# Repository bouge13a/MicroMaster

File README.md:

# The Next Generation of Hardware Hacking Tools
* The MicroMaster Mini, like the Bus-Pirate, Shikra, and Hydrabus before it, is a small circuit board that communicates to a computer via a Virtual COM port.
* The purpose of the MicroMaster Mini is to allow the user to test commands that may be sent from a master to a slave device using a variety of protocols such as UART, CAN, I2C, SMBUS, SPI, 1-Wire, WS2812 (neopixel) and PWM. The MicroMaster Mini also allows the user to "sniff" CAN, SMBUS, UART, and I2C transactions.
* Unlike the Bus-Pirate and Bus-Pirate derived devices, the MicroMaster Mini employs a highly sophisticated serial interface that has a system of pages similar to a web browser that can be navigated and manipulated with an ASCII keyboard. 
* Allows users to monitor the registers of I2C devices and SPI devices in real time. 
* Has an integrated help feature for each page which describes the purpose and operation of each page. The MicroMaster Mini does not require a manual for use. 
* Allows the user to easily manipulate 4 GPOs and monitor 4 GPIs and 4 ADCs. 
* Operates as an FTDI chip emulator so that the user can transmit UART signals to a USB virtual COM port. 
* Has a suite of neopixel control tools which allow the user to easily control up to 999 neopixels!
* Programmable power supply to 2v8 3v3 and 5v. The I2C bus also level shifts with the power supply. 
* The entire project is open sourced. 
* The MicroMaster Mini is based upon the TM4C123GXL launchpad and will run on a launchpad with some minor modifications. The code is written in C++ with FreeRTOS in the Code Composer Studio IDE.

Check out the demonstration video as well as other videos on the channel. Please like and subscribe for future videos. 

MicroMaster Mini Interface Demonstration (early version)
https://www.youtube.com/watch?v=Cxuv18Nnr2U&t=313s

Controlling Neopixels with the MicroMaster Mini
https://www.youtube.com/watch?v=bUdS3NqcU9w&t=137s

# Test and Build
The firmware will run on a TM4C123GXL launchpad. The following steps are the easiest way to test and build the MicroMaster Mini on a launchpad for testing. 

* Connect both USB ports to the host computer.
* Flash the .out file in the Debug directory to the TM4C123GXL using LMFlash (found on TI website)
* Set up a virtual COM port with the TM4C using Putty
* Start testing the MicroMaster Mini firmware! 
* Find a bug and report an issue.

Note: Some resistors will have to be removed from the launchpad to get full functionality (R9 and R10). The I2C sniffer will not work unless these resistors are removed.

# Get Involved!
The MicroMaster Mini is still very much under development. The purpose of making this project open sourced is to get the community involved. There is still a ton of work to do. If you have any of the following skills and would like to contribute, please email me at stephan@micromaster.io. I am very responsive, so don't hesitate to reach out. 

* C++ and FreeRTOS (expert)
* Bootloaders (OpenBLT)
* OpenOCD
* Web Design
* Testing and verification (open to all skill levels)
* Marketing
* Hardware Design
* Fundraising

# ScreenShots

Here is the first screen that comes up after the terminal detects a keystroke. The power supply is adjustable with the arrow keys and the user can press a corresponding letter to get to a tool suite. 

Here is the main suite of tools that are currently offered by the MicroMaster Mini. Press any letter to jump to a page or press TAB to toggle the pages. Press ESC to return to homepage. 

This is the configuration menu of the MicroMaster Mini. The user can select the configuration options by using the arrow keys

Here is an example of a transaction that was sent in I2C command. The transaction was set up so that it can be monitored on the next page. 

Here is the i2c monitor after a monitored transaction was sent. The value is periodically updated in real time. It can be converted to binary, hexidecimal, LSB decimal or MSB decimal with the arrow keys

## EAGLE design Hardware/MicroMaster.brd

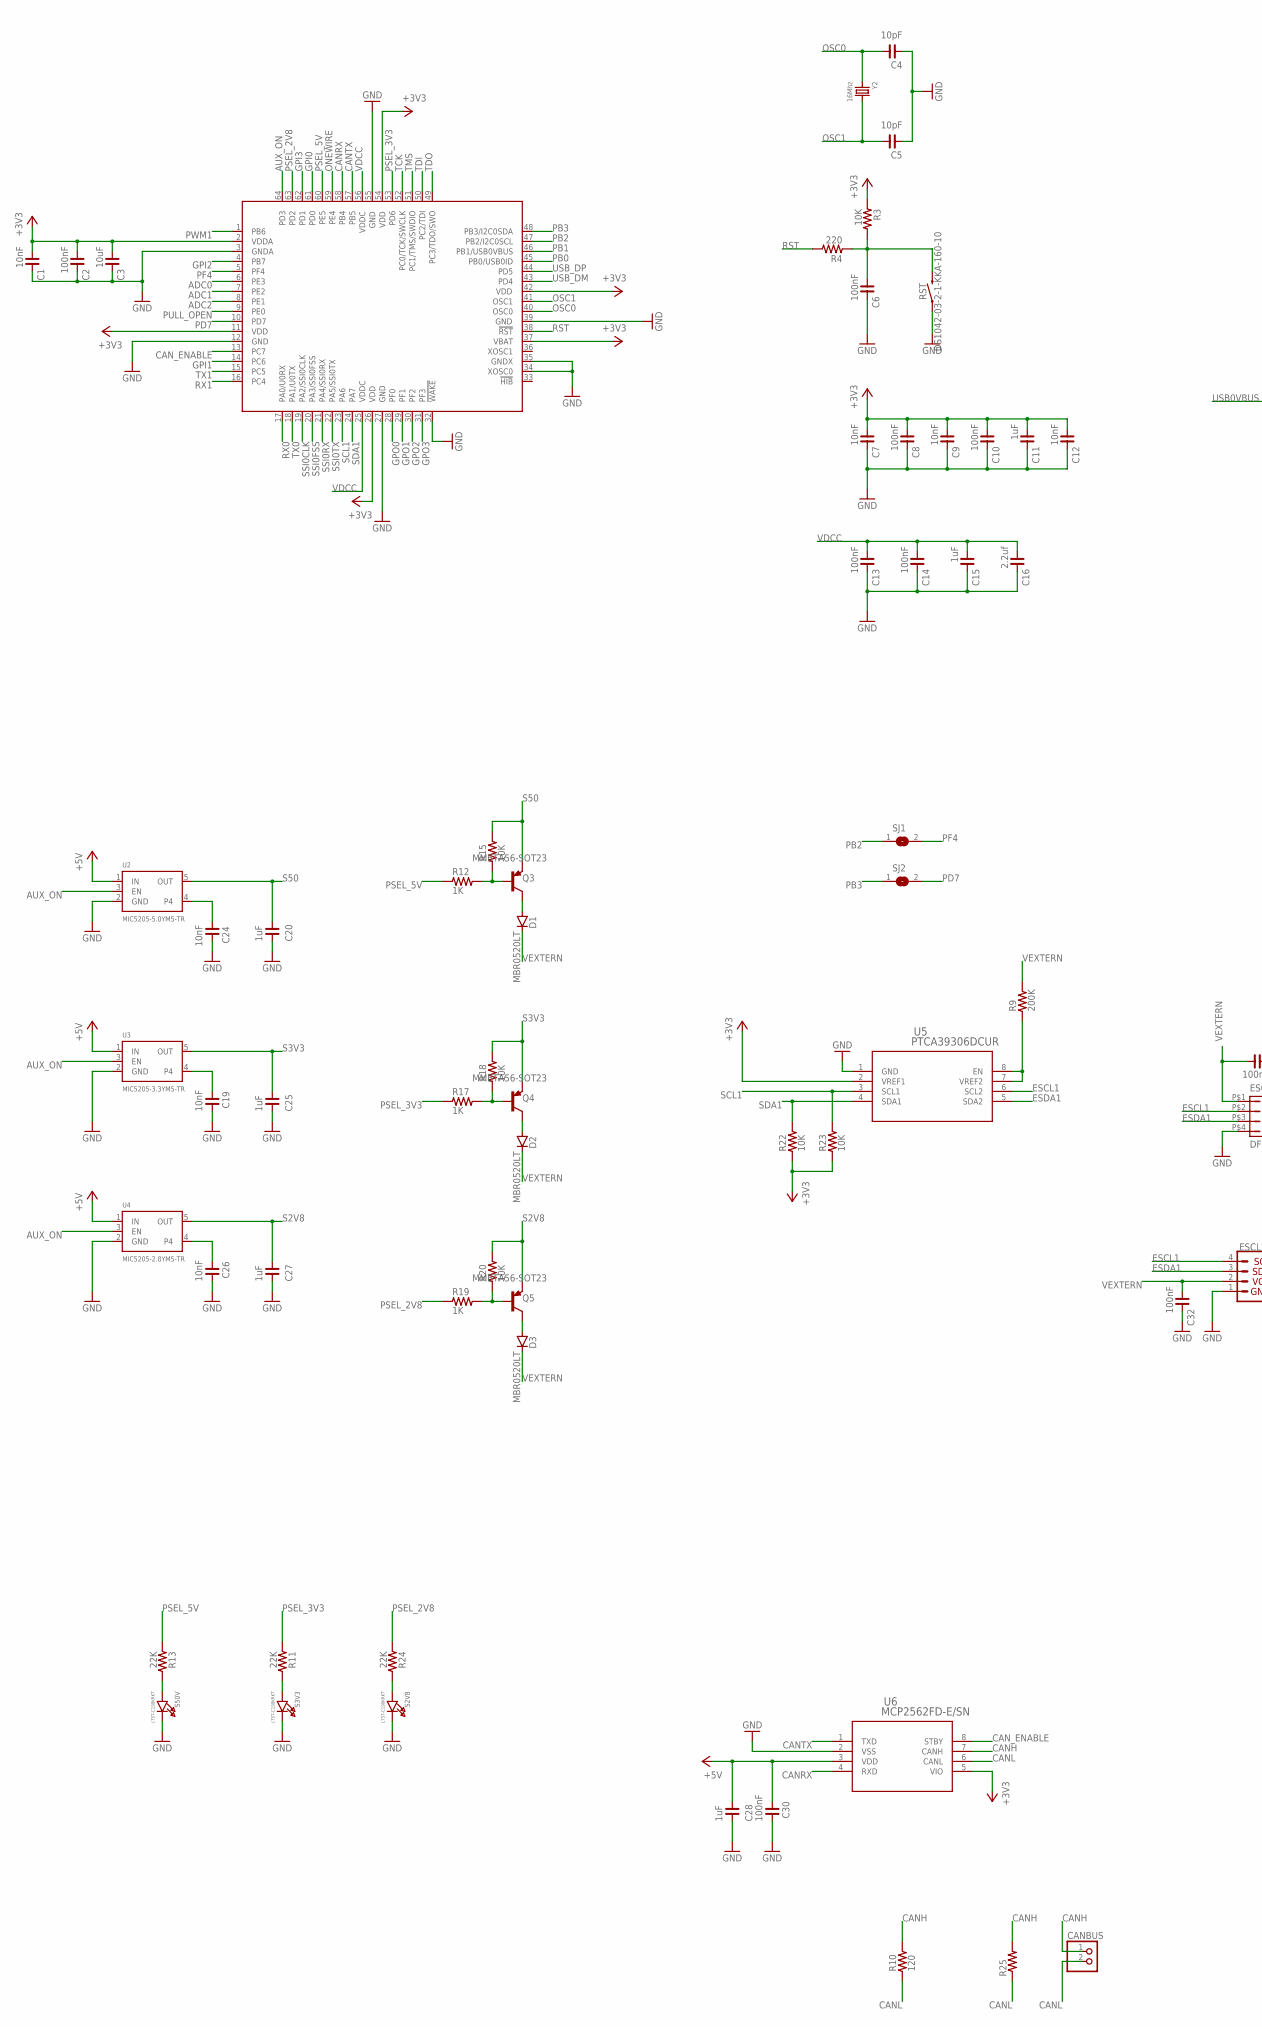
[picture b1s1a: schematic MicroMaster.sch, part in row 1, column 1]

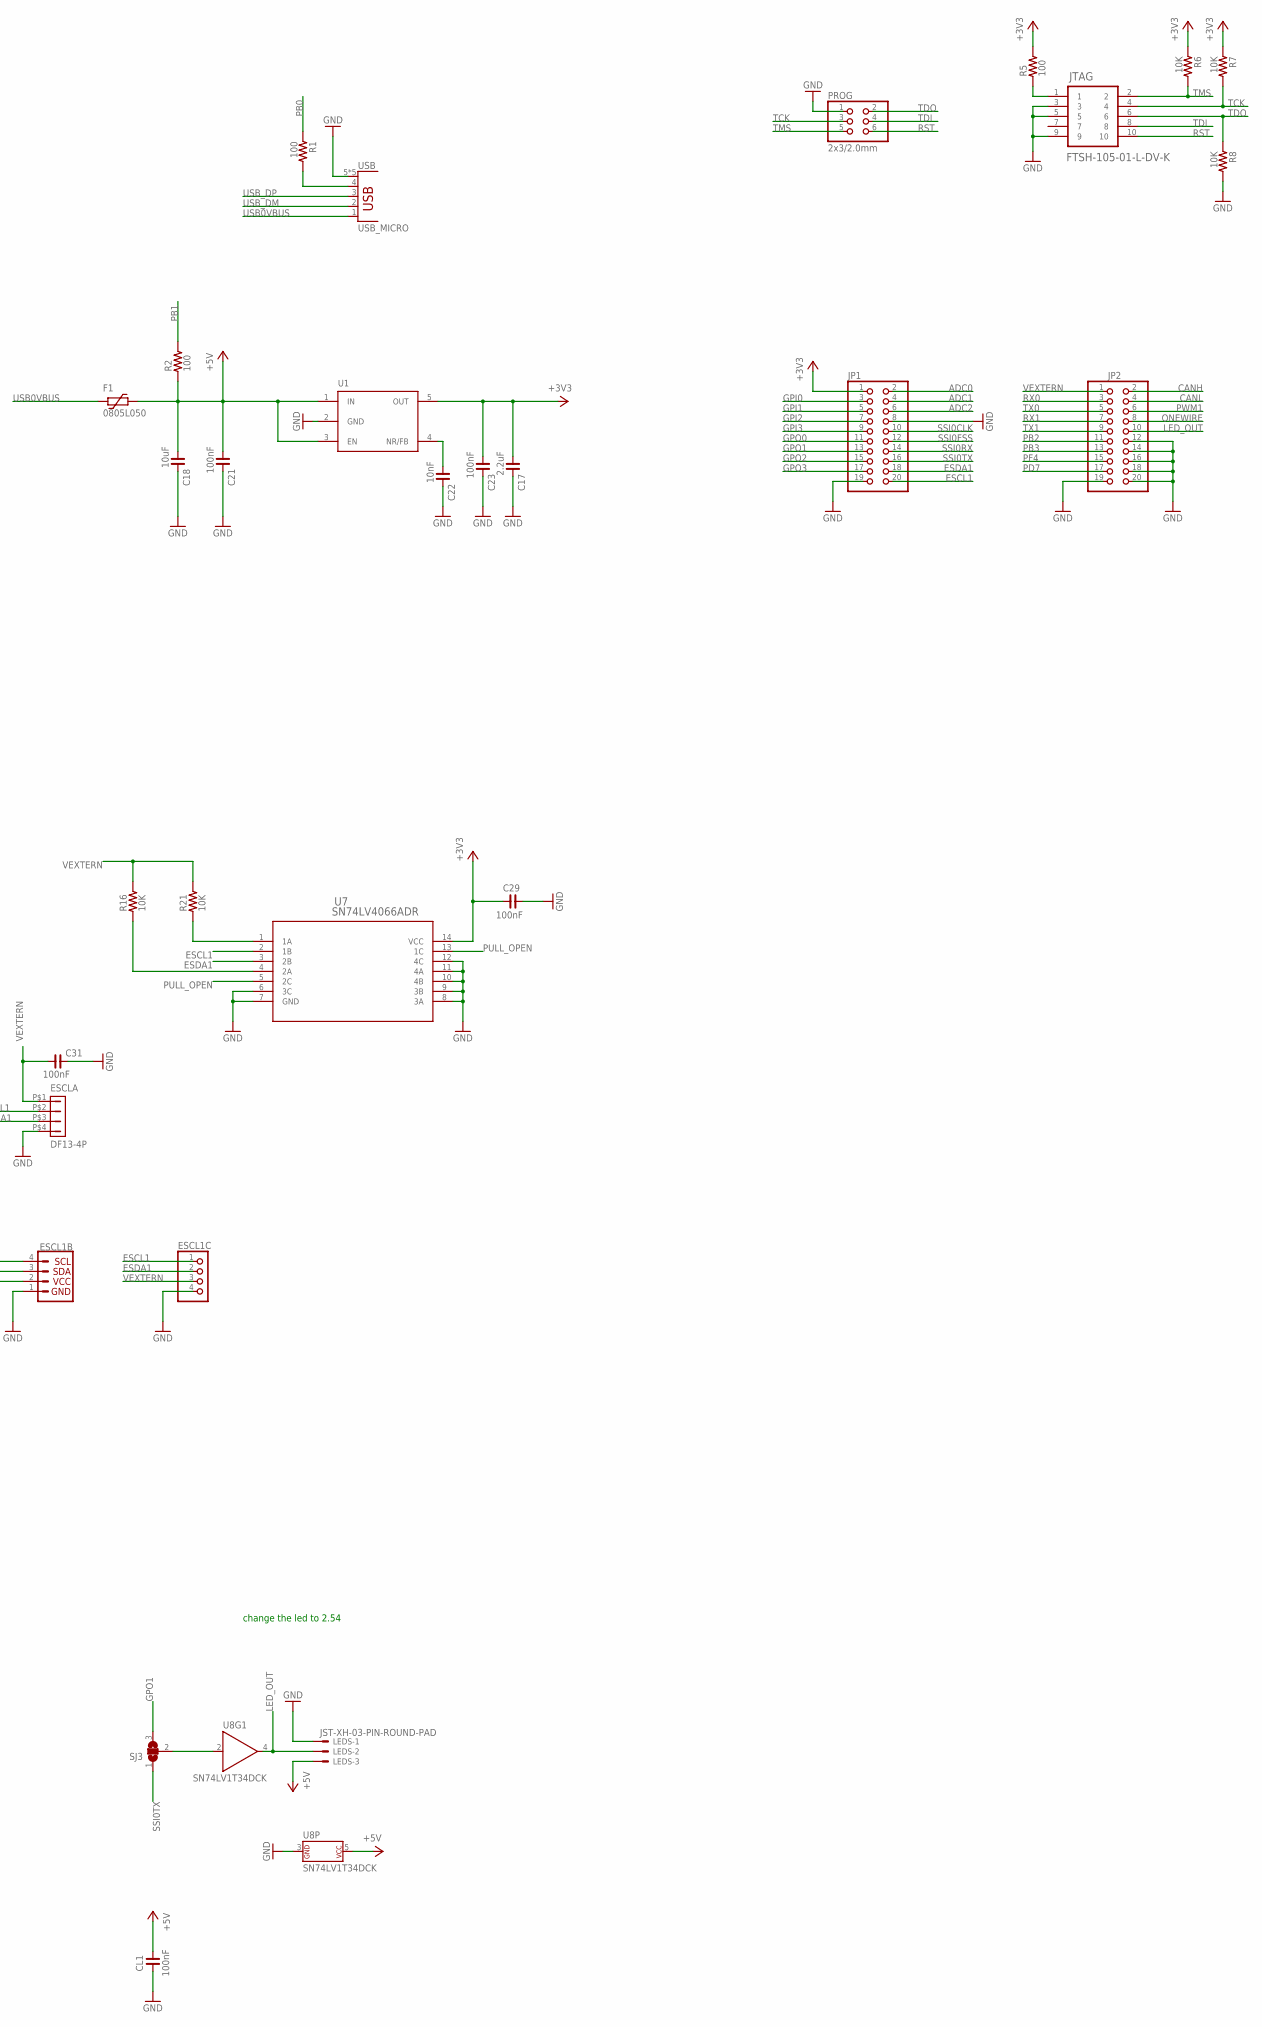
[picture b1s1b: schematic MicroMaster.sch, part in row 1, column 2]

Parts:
C1, C7, C9, C12, C19, C22, C24, C26: 10nF; C0402
C2, C6, C8, C10, C13, C14, C21, C23, C31, C32: 100nF; C0402
C3, C18: 10uF; C0603
C4, C5: 10pF; C0402
C11, C15: 1uF; C0402
C16: 2.2uf; C0603
C17: 2.2uF; C0603
C20, C25, C27: 1uF; C0603
C28: 1uF; C0805
C29, C30: 100nF; C0603
CANBUS: PINHD-1X02_2.54-S; 1X02-S
CL1: 100nF; C0402
D1, D2, D3: MBR0520LT; SOD123
ESCL1B: QWIIC_CONNECTORJS-1MM; 1X04_1MM_RA
ESCL1C: PINHD-1X04_2.54-S; 1X04-S
ESCLA: DF13-4P; DF13-4P-1.25DSA
F1: 0805L050; 0805L
IC1: TM4C123[7,G]XXPM; PM_S-PQFP-G64
JP1, JP2: PINHD-2X10_2.54; 2X10
JTAG: FTSH-105-01-L-DV-K; SAMTEC_FTSH-105-01-L-DV-K
LEDS: JST-XH-03-PIN-ROUND-PAD; JST-XH-03-PACKAGE-ROUND-PAD
PROG: 2x3/2.0mm; 2X03M
Q3, Q4, Q5: MMBTA56-SOT23; SOT23
R1, R2, R5: 100; R0402
R3, R6, R7, R8, R15, R16, R18, R20, R21, R22, R23: 10K; R0402
R4: 220; R0402
R9: 200K; R0402
R10: 120; R0603
R11, R13, R24: 22K; R0402
R12, R17, R19: 1K; R0402
R25: R-US_0204/5; 0204/5
RST: DS1042-03-2-1-KKA-160-10; DS1042-03-2-1
S2V8, S3V3, S50V: LTST-C190KRKT; CHIPLED_0603
SJ1, SJ2: SOLDERJUMPERCLOSED; SOLDERJUMPER_CLOSEDWIRE
SJ3: SJ2W; SJ_2
U1: TPS73633; SOT23-5L
U2: MIC5205-5.0YM5-TR; SOT23-5
U3: MIC5205-3.3YM5-TR; SOT23-5
U4: MIC5205-2.8YM5-TR; SOT23-5
U5: PTCA39306DCUR; VSSOP8_PTCA39306DCUR_TEX
U6: MCP2562FD-E/SN; SOIC8-N_MC_MCH
U7: SN74LV4066ADR; D14
U8: SN74LV1T34DCK; SC70-5
USB: USB_MICRO; USB_MICRO_MOLEX_FULL
Y2: 16Mhz; 6X3.3MM

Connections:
+3V3: C1.1, C2.1, C3.1, C7.1, C8.1, C9.1, C10.1, C11.1, C12.1, C17.1, C23.1, C29.1, IC1.2 (VDDA), IC1.11 (VDD), IC1.26 (VDD), IC1.37 (VBAT), IC1.42 (VDD), IC1.54 (VDD), JP1.1, R3.1, R5.2, R6.1, R7.1, R22.1, R23.1, U1.5 (OUT), U5.2 (VREF1), U6.5 (VIO), U7.14 (VCC)
ADC0: IC1.6 (PE3), JP1.2
ADC1: IC1.7 (PE2), JP1.4
ADC2: IC1.8 (PE1), JP1.6
AUX_ON: IC1.64 (PD3), U2.3 (EN), U3.3 (EN), U4.3 (EN)
CANH: CANBUS.1, JP2.2, R10.2, R25.2, U6.7 (CANH)
CANL: CANBUS.2, JP2.4, R10.1, R25.1, U6.6 (CANL)
CANRX: IC1.58 (PB4), U6.4 (RXD)
CANTX: IC1.57 (PB5), U6.1 (TXD)
CAN_ENABLE: IC1.13 (PC7), U6.8 (STBY)
ESCL1: ESCL1B.4, ESCL1C.1, ESCLA.P$2 (2), JP1.20, U5.6 (SCL2), U7.2 (1B)
ESDA1: ESCL1B.3, ESCL1C.2, ESCLA.P$3 (3), JP1.18, U5.5 (SDA2), U7.3 (2B)
GND: C1.2, C2.2, C3.2, C4.1, C5.1, C6.2, C7.2, C8.2, C9.2, C10.2, C11.2, C12.2, C13.2, C14.2, C15.2, C16.2, C17.2, C18.2, C19.2, C20.2, C21.2, C22.2, C23.2, C24.2, C25.2, C26.2, C27.2, C28.2, C29.2, C30.2, C31.2, C32.2, CL1.1, ESCL1B.1, ESCL1C.4, ESCLA.P$4 (4), IC1.3 (GNDA), IC1.12 (GND), IC1.27 (GND), IC1.32 (!WAKE), IC1.34 (XOSC0), IC1.35 (GNDX), IC1.39 (GND), IC1.55 (GND), JP1.8, JP1.19, JP2.12, JP2.14, JP2.16, JP2.18, JP2.19, JP2.20, JTAG.3, JTAG.5, JTAG.9, LEDS.1, PROG.1, R8.2, RST.P$1 (1), S2V8.C, S3V3.C, S50V.C, U1.2 (GND), U2.2 (GND), U3.2 (GND), U4.2 (GND), U5.1 (GND), U6.2 (VSS), U7.6 (3C), U7.7 (GND), U7.8 (3A), U7.9 (3B), U7.10 (4B), U7.11 (4A), U7.12 (4C), U8.3 (P$V-), USB.5 (GND), USB.P$1 (GND), USB.P$2 (GND), USB.P$3 (GND), USB.P$4 (GND)
GPI0: IC1.61 (PD0), JP1.3
GPI1: IC1.14 (PC6), JP1.5
GPI2: IC1.4 (PB7), JP1.7
GPI3: IC1.62 (PD1), JP1.9
GPO0: IC1.28 (PF0), JP1.11
GPO1: IC1.29 (PF1), JP1.13, SJ3.3
GPO2: IC1.30 (PF2), JP1.15
GPO3: IC1.31 (PF3), JP1.17
LED_OUT: JP2.10, LEDS.2, U8.4 (Y)
unnamed: C19.1, U3.4
unnamed: JTAG.1, R5.1
unnamed: C6.1, R3.2, R4.1, RST.P$2 (2)
unnamed: R21.1, U7.1 (1A)
unnamed: R1.2, USB.4 (ID)
unnamed: R9.1, U5.7 (VREF2), U5.8 (EN)
unnamed: R16.1, U7.4 (2A)
unnamed: R24.2, S2V8.A
unnamed: C24.1, U2.4
unnamed: R11.2, S3V3.A
unnamed: C26.1, U4.4
unnamed: R13.2, S50V.A
unnamed: SJ3.2, U8.2 (A)
unnamed: C22.1, U1.4 (NR/FB)
unnamed: D1.A, Q3.3 (C)
unnamed: Q3.1 (B), R12.2, R15.1
unnamed: D2.A, Q4.3 (C)
unnamed: Q4.1 (B), R17.2, R18.1
unnamed: D3.A, Q5.3 (C)
unnamed: Q5.1 (B), R19.2, R20.1
ONEWIRE: IC1.59 (PE4), JP2.8
OSC0: C4.2, IC1.40 (OSC0), Y2.1
OSC1: C5.2, IC1.41 (OSC1), Y2.2
PB0: IC1.45 (PB0/USB0ID), R1.1
PB1: IC1.46 (PB1/USB0VBUS), R2.2
PB2: IC1.47 (PB2/I2C0SCL), JP2.11, SJ1.1
PB3: IC1.48 (PB3/I2C0SDA), JP2.13, SJ2.1
PD7: IC1.10 (PD7), JP2.17, SJ2.2
PF4: IC1.5 (PF4), JP2.15, SJ1.2
PSEL_2V8: IC1.63 (PD2), R19.1, R24.1
PSEL_3V3: IC1.53 (PD6), R11.1, R17.1
PSEL_5V: IC1.60 (PE5), R12.1, R13.1
PULL_OPEN: IC1.9 (PE0), U7.5 (2C), U7.13 (1C)
PWM1: IC1.1 (PB6), JP2.6
RST: IC1.38 (!RST), JTAG.10, PROG.6, R4.2
RX0: IC1.17 (PA0/U0RX), JP2.3
RX1: IC1.16 (PC4), JP2.7
S2V8: C27.1, Q5.2 (E), R20.2, U4.5 (OUT)
S3V3: C25.1, Q4.2 (E), R18.2, U3.5 (OUT)
S50: C20.1, Q3.2 (E), R15.2, U2.5 (OUT)
SCL1: IC1.23 (PA6), R23.2, U5.3 (SCL1)
SDA1: IC1.24 (PA7), R22.2, U5.4 (SDA1)
SSI0CLK: IC1.19 (PA2/SSI0CLK), JP1.10
SSI0FSS: IC1.20 (PA3/SSI0FSS), JP1.12
SSI0RX: IC1.21 (PA4/SSI0RX), JP1.14
SSI0TX: IC1.22 (PA5/SSI0TX), JP1.16, SJ3.1
TCK: IC1.52 (PC0/TCK/SWCLK), JTAG.4, PROG.3, R7.2
TDI: IC1.50 (PC2/TDI), JTAG.8, PROG.4
TDO: IC1.49 (PC3/TDO/SWO), JTAG.6, PROG.2, R8.1
TMS: IC1.51 (PC1/TMS/SWDIO), JTAG.2, PROG.5, R6.2
TX0: IC1.18 (PA1/U0TX), JP2.5
TX1: IC1.15 (PC5), JP2.9
USB0VBUS: F1.2, USB.1 (VBUS)
USB05V: C18.1, C21.1, C28.1, C30.1, CL1.2, F1.1, LEDS.3, R2.1, U1.1 (IN), U1.3 (EN), U2.1 (IN), U3.1 (IN), U4.1 (IN), U6.3 (VDD), U8.5 (P$V+)
USB_DM: IC1.43 (PD4), USB.2 (D-)
USB_DP: IC1.44 (PD5), USB.3 (D+)
VDCC: C13.1, C14.1, C15.1, C16.1, IC1.25 (VDDC), IC1.56 (VDDC)
VEXTERN: C31.1, C32.1, D1.C, D2.C, D3.C, ESCL1B.2, ESCL1C.3, ESCLA.P$1 (1), JP2.1, R9.2, R16.2, R21.2

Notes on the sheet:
change the led to 2.54

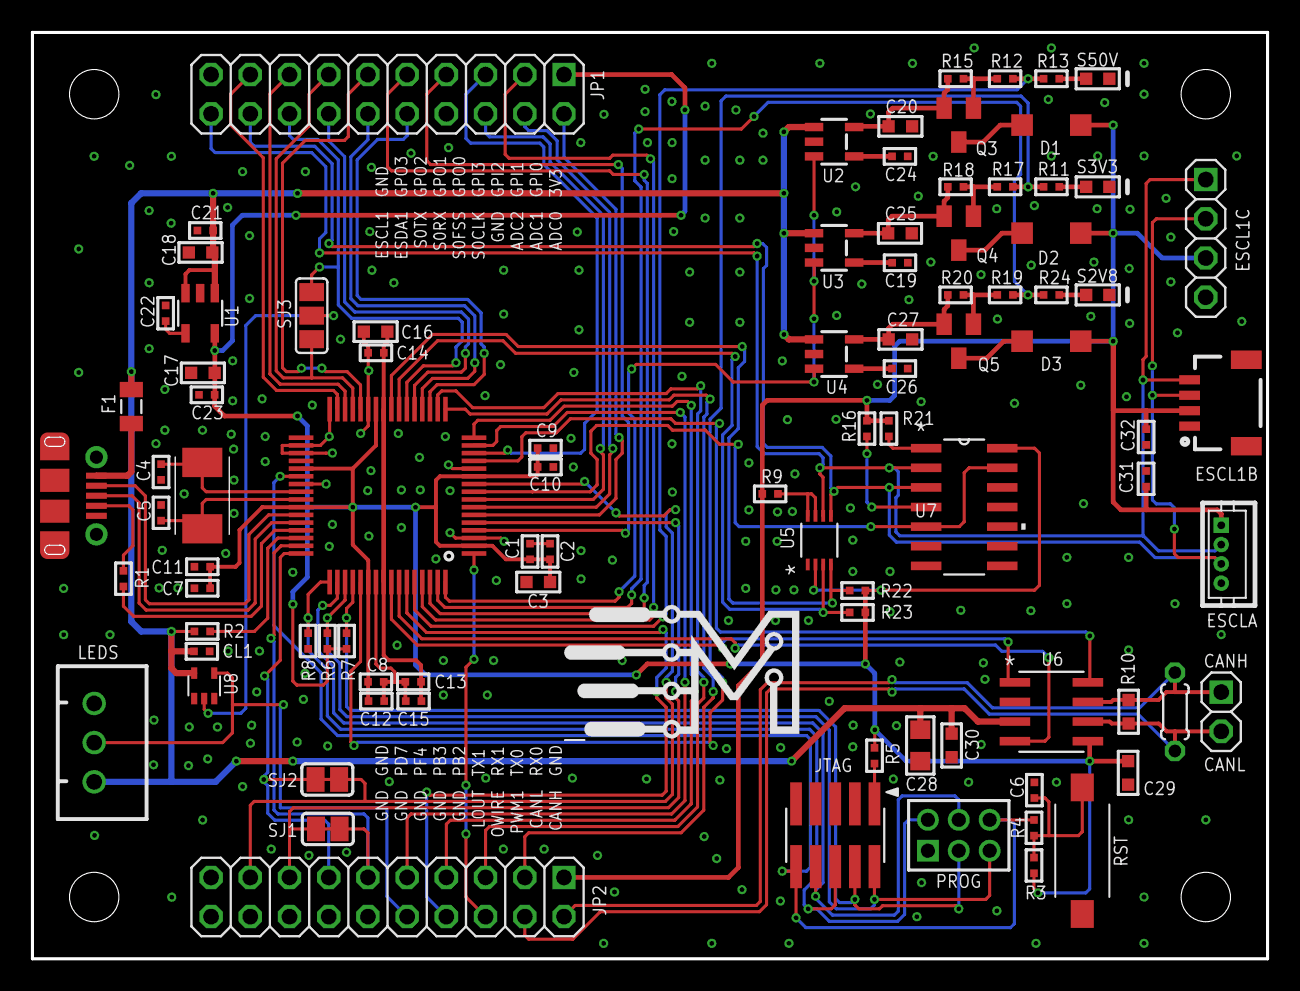
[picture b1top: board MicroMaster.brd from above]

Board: 2 copper layers, 80.0 x 60.0 mm, 91 parts (0 on the bottom side), 80 nets.

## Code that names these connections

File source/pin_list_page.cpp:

/*
 * pin_list_page.cpp
 *
 *  Created on: Feb 11, 2022
 *      Author: steph
 */

#include "pin_list_page.hpp"

#include <stdint.h>
#include "uartstdio.h"

#include "text_controls.hpp"

typedef struct {
    const char* pin_num;
    const char* description;
}pin_descr_t;

static const pin_descr_t pin_descriptions[] = {
    {"PA2", "SPI Clock"},
    {"PA3", "SPI Chip Select"},
    {"PA4", "SPI Rx"},
    {"PA5", "SPI Tx"},
    {"PA6", "I2C SCL"},
    {"PA7", "I2C SDA"},
    {"PB2", "I2C Sniffer SCL"},
    {"PB3", "I2C Sniffer SDA"},
    {"PB4", "CAN Rx"},
    {"PB5", "CAN Tx"},
    {"PB6", "PWM"},
    {"PC4", "UART Rx"},
    {"PC5", "UART Tx"},
    {"PD0", "GPI 0"},
    {"PC6", "GPI 1"},
    {"PB7", "GPI 2"},
    {"PD1", "GPI 3"},
    {"PF0", "GPO 0"},
    {"PF1", "GPO 1"},
    {"PF2", "GPO 2"},
    {"PF3", "GPO 3"},
    {"PE3", "ADC 0"},
    {"PE2", "ADC 1"},
    {"PE1", "ADC 2"},
};

static const uint32_t pin_descriptions_size = sizeof(pin_descriptions)/sizeof(pin_descriptions[0]);

static const uint32_t DESCR_COL = 8;
static const uint32_t SECOND_START_COL = 50;
static const uint32_t START_ROW = 6;

PinPage::PinPage(void) : ConsolePage("Pin List",
                                      portMAX_DELAY,
                                      false) {

}

void PinPage::draw_page(void) {

    TextCtl::cursor_pos(START_ROW, 0);
    UARTprintf("Pin");
    TextCtl::cursor_pos(START_ROW, DESCR_COL);
    UARTprintf("Description");
    TextCtl::cursor_pos(START_ROW, SECOND_START_COL);
    UARTprintf("Pin");
    TextCtl::cursor_pos(START_ROW, DESCR_COL + SECOND_START_COL);
    UARTprintf("Description");

    for (uint32_t index=0; index<pin_descriptions_size; index++) {

        if (index < pin_descriptions_size/2) {

            TextCtl::cursor_pos(START_ROW + 2 + index, 0);
            UARTprintf("%s", pin_descriptions[index].pin_num);
            TextCtl::cursor_pos(START_ROW + 2 + index, DESCR_COL);
            UARTprintf("%s", pin_descriptions[index].description);

        } else {

            TextCtl::cursor_pos(START_ROW + 2 + index - pin_descriptions_size/2, SECOND_START_COL);
            UARTprintf("%s", pin_descriptions[index].pin_num);
            TextCtl::cursor_pos(START_ROW + 2 + index - pin_descriptions_size/2, DESCR_COL + SECOND_START_COL);
            UARTprintf("%s", pin_descriptions[index].description);

        }
    }
}
void PinPage::draw_data(void) {

}
void PinPage::draw_input(int character) {

}
void PinPage::draw_help(void) {

}
void PinPage::draw_reset(void) {

}

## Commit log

2021-07-12 added FreeRTOS needs testing
2021-08-03 initial commit, code working, just added scripter
2021-08-03 Added I2C sniffer and monitor format specifiers
2021-08-03 fixed bugs in i2c monitor format
2021-08-03 Added ADC GPIO
2021-08-04 Added heap 4 and configuration menu
2021-08-05 fixed binary bug and started PWM module
2021-08-05 Added help and reset functions
2021-08-05 fixed i2c monitor bug
2021-08-06 added PWM tested and added error logger clear'
2021-08-06 added reset to PWM
2021-08-08 fixed i2c command letter bug
2021-08-09 started SPI command
2021-08-09 WIP working on SPI command
2021-08-11 WIP fixed tx byte print bug
2021-08-11 fixed some bugs, still doesnt work
2021-08-12 Added spi mode menu
2021-08-13 Added data width, mode and speed to SPI WIP
2021-08-13 fixed some bugs its friday Im tired
2021-08-23 Fixed SPI working on SPI monitor
2021-08-23 SPI monitor works needs rx testing
2021-08-23 added SPI max frequency
2021-08-23 WIP added UART streamer and command
2021-08-24 UART streamer is working
2021-08-24 added uart menu and uart command WIP
2021-08-24 fixed uart hex bug
2021-08-25 Added byte mode to uart
2021-08-25 fixed some bugs about to match pins to schematic
2021-08-25 updated board to schematic added power options
2021-08-25 about to convert to USB serial
2021-08-26 added uart to usb needs clean up
2021-08-26 cleaned up usb to uart, added any key
2021-08-26 Started one wire command
2021-08-27 added one wire command, needs testing
2021-08-27 Added TI and MicroWire to SPI
2021-08-28 one wire driver is functional but does not read
2021-08-28 One wire command works, needs clean up
2021-08-30 Made one wire take in 20 tx bytes
2021-08-30 started one wire search and trimmed stack size
2021-08-31 started one wire search and fixed bugs in ioctl and one wire command
2021-08-31 fixed one digit byte bug and I2C scripter
2021-08-31 fixed i2c scripter for real this time
2021-09-01 fixed monitor double print bug
2021-09-01 Started CAN command
2021-09-01 still working on CAN command
2021-09-02 Added CAN command, needs testing
2021-09-02 CAN needs testing, CAN sniffer added
2021-09-03 added one wire search algorithm WIP
2021-09-04 one wire search can do one device but not multiple
2021-09-05 one wire search almost works
2021-09-05 ONE WIRE SEARCH ALGORITHM WORKS!"
2021-09-07 upped proc speed to 80MHz and fixed some bugs
2021-09-07 fixed some bugs, starting i2c sniffer
2021-09-07 updated PWM page, still has bugs
2021-09-08 fixed some bugs with PWM, still needs work
2021-09-08 Added introduction page
2021-09-08 Made one wire recognize devices
2021-09-14 fixed PWM bugs and added servo mode
2021-09-15 Added i2c sniffer WIP
2021-09-16 WIP i2c sniffer needs to be on a single port with a single interrupt
2021-09-16 I2C sniffer works, but not with Clock stretching
2021-09-17 added nine clock to i2c, bus still hangs with sniffer
2021-09-24 CAN works, needs adjustable speed
2021-09-27 WIP added num converter
2021-10-04 fixed i2c search errors
2021-10-04 fixed problems with num converter
2021-10-05 made power supply select at begining
2021-10-05 added ftdi emulator program
2021-10-05 fixed uart streamer
2021-10-06 fized bugs in num converter
2021-10-07 added alarm bell to unrecognized chars
2021-10-08 started neopixel, switching to SPI
2021-10-09 added SPI neopixel driver
2021-10-14 added neopixel ctl
2021-10-18 fixed i2c search bug
2021-10-20 added rgb control
2021-10-21 fixed neopixel driver
2021-10-23 added neopixel menu
2021-10-24 added more neopix functions
2021-10-24 added rgbx option
2022-02-08 Initial commit to github
2022-02-09 added docs and images folders
2022-02-09 added hardware files
2022-02-09 Create LICENSE
2022-02-09 fixed ps menu
2022-02-11 Added pin list page and some help pages to i2c
2022-07-09 Fixed pins and deleted hardware
2022-07-09 fixed pin init bug
2022-07-09 added libraries and uartstdio to project
2022-07-09 fixed strange compilation bugs
2022-07-09 cproject fix
2022-07-09 git to ignore Debug
2022-07-09 psu issue fixed
2022-07-10 removed gpi 0 and 3 and added I2C_auc
2022-07-16 Fixed bug in main menu
2022-07-16 THIS COMMIT IS BROKEN!!!
2022-07-16 Current monitor is talking but it returns 0
2022-07-16 Current monitor is working
2022-07-16 Added semaphore to I2cMsgAux
2022-07-17 created binary release folder
2022-07-17 Added display task
2022-07-17 added logger and menu to display vector
2022-07-17 Added MM ascii art
2022-07-20 Added graphix library and integrate current to display
2022-07-20 totally confused about i2c msg queue
2022-07-21 Fixed stupid display bug
2022-07-22 Added psu and pull to display

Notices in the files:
parts and their libraries:
microbuilder: This work is placed in the public domain, and may be freely used for commercial and non-commercial work with the following conditions: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
rc-master-smd: Copyright (C) 2007, Bob Starr
COPYRIGHT: Copyright (C) 2021 Ultra Librarian. All rights reserved.
